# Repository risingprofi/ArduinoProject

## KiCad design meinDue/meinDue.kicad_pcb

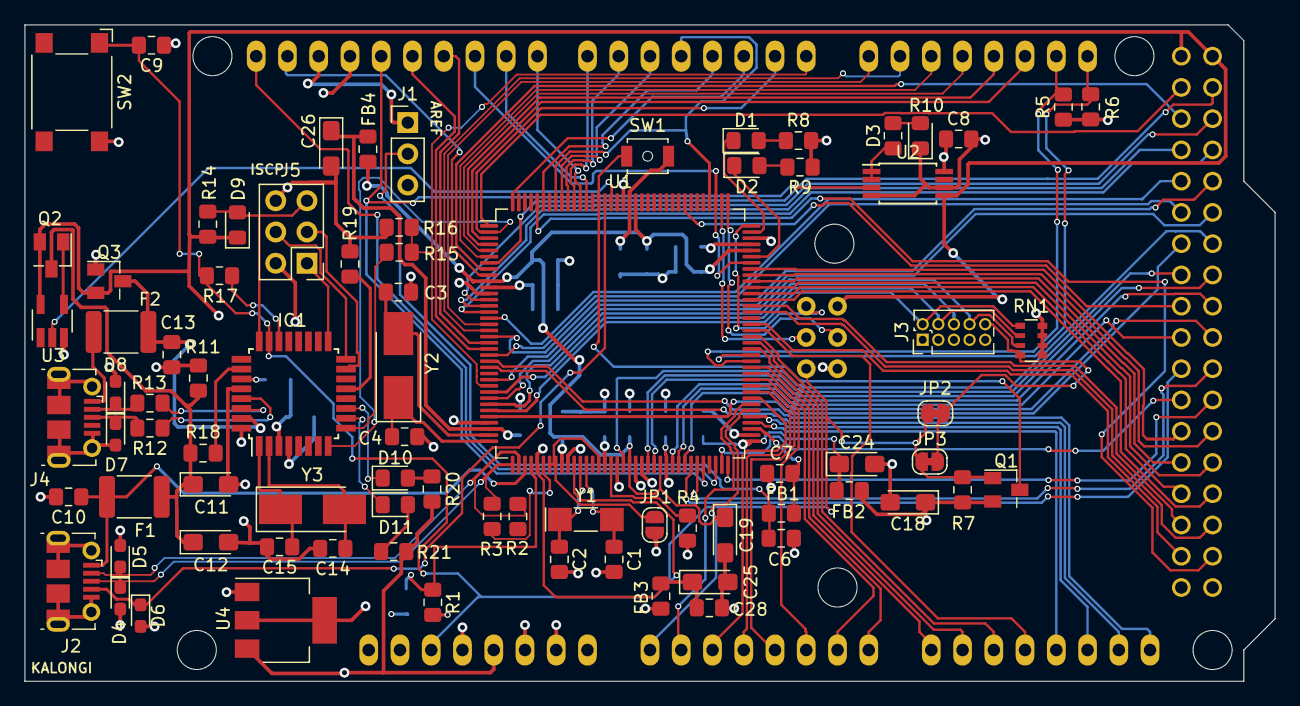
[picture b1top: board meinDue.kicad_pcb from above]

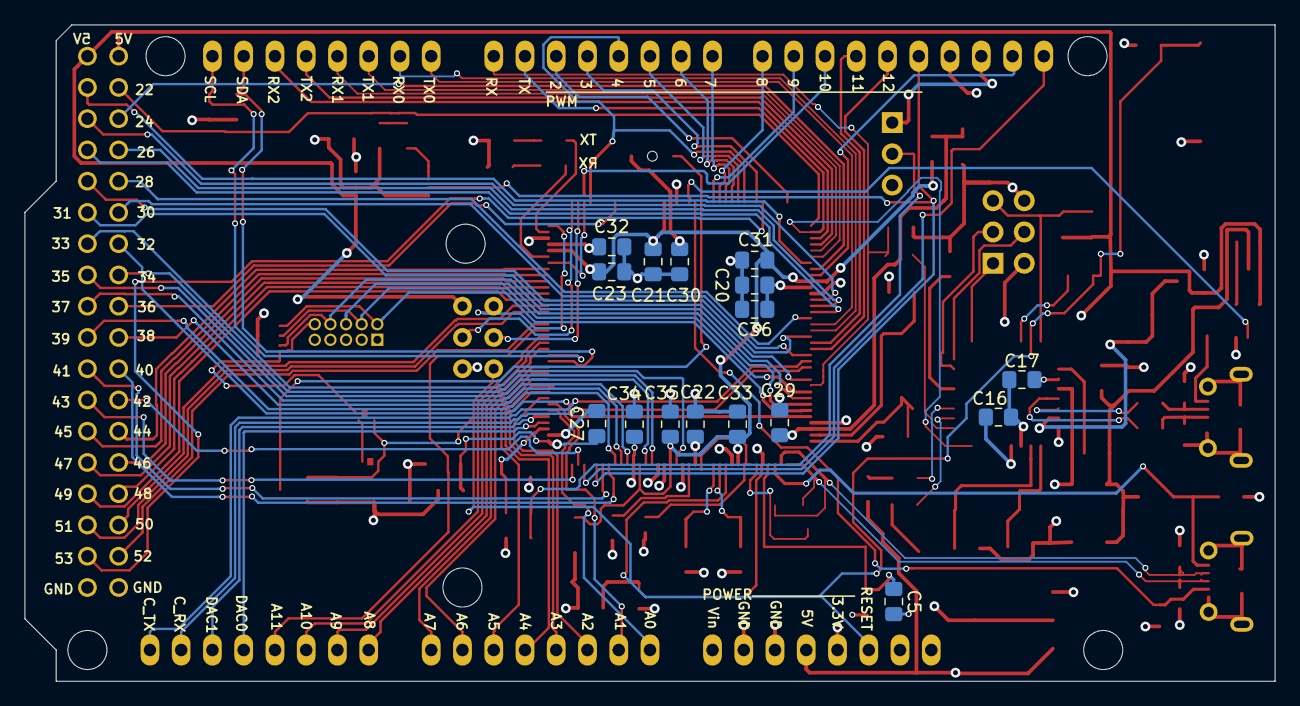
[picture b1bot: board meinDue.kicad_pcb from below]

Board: 4 copper layers, 101.6 x 53.3 mm, 97 parts (16 on the bottom side), 134 nets.

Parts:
C1, C2, C3, C4, C5, C14, C15: 22pF; C_0805_2012Metric_Pad1.15x1.40mm_HandSolder
C6, C7, C8, C9, C13, C16, C20, C21, C22, C23, C27, C28, C29, C30, C31, C32, C33, C34, C35, C36: 100nF; C_0805_2012Metric_Pad1.15x1.40mm_HandSolder
C10: 10nF; C_0805_2012Metric_Pad1.15x1.40mm_HandSolder
C11, C12, C18, C19, C24, C25, C26: 10uF; CP_EIA-3216-18_Kemet-A_Pad1.58x1.35mm_HandSolder
C17: 1uF; C_0805_2012Metric_Pad1.15x1.40mm_HandSolder
D1, D2, D3, D10, D11: YELLOW; LED_0805_2012Metric_Pad1.15x1.40mm_HandSolder
D4, D5, D6, D7, D8: D_TVS; D_0603_1608Metric_Pad1.05x0.95mm_HandSolder
D9: D; D_0805_2012Metric_Pad1.15x1.40mm_HandSolder
F1, F2: Polyfuse; Fuse_1812_4532Metric_Pad1.30x3.40mm_HandSolder
FB1, FB2, FB3, FB4: Ferrite_Bead; L_0805_2012Metric_Pad1.15x1.40mm_HandSolder
IC1: ATMEGA16U2; TQFP-32_7x7mm_P0.8mm
J1: Conn_01x03; PinHeader_1x03_P2.54mm_Vertical
J2, J4: USB_B_Micro; USB_Micro-B_Molex-105017-0001
J3: Conn_02x05_Odd_Even; PinHeader_2x05_P1.27mm_Vertical
J5: ICSP; PinHeader_2x03_P2.54mm_Vertical
JP1: SolderJumper_2_Open; SolderJumper-2_P1.3mm_Open_RoundedPad1.0x1.5mm
JP2, JP3: SolderJumper_2_Bridged; SolderJumper-2_P1.3mm_Bridged_RoundedPad1.0x1.5mm
Q1, Q2, Q3: Q_PMOS_GSD; SuperSOT-3
R1: 6k8 1%; R_0805_2012Metric_Pad1.15x1.40mm_HandSolder
R2, R3: 39R 1%; R_0805_2012Metric_Pad1.15x1.40mm_HandSolder
R4: 100K; R_0805_2012Metric_Pad1.15x1.40mm_HandSolder
R5, R6, R15: 1K5; R_0805_2012Metric_Pad1.15x1.40mm_HandSolder
R7, R11, R14, R19: 10K; R_0805_2012Metric_Pad1.15x1.40mm_HandSolder
R8, R9, R10, R17, R18, R20, R21: 1K; R_0805_2012Metric_Pad1.15x1.40mm_HandSolder
R12, R13: 22R; R_0805_2012Metric_Pad1.15x1.40mm_HandSolder
R16: 2K7; R_0805_2012Metric_Pad1.15x1.40mm_HandSolder
RN1: 100K; R_Array_Convex_4x0603
SHIELD1: ARDUINO_DUE_SHIELD - SPI; ARDUINO_DUE_SHIELD
SW1: SW_SPST; SW_SPST_B3U-1000P-B
SW2: SW_SPST; SW_SPST_Omron_B3FS-100xP
U1: ATSAM3X8E; LQFP-144_20x20mm_P0.5mm
U2: LM358; TSSOP-8_4.4x3mm_P0.65mm
U3: 74LVC1G04; SOT-23-5_HandSoldering
U4: NCP1117ST33T3G; SOT-223-3_TabPin2
Y1: ABS07L 32.768kHz; Crystal_SMD_MicroCrystal_CC5V-T1A-2Pin_4.1x1.5mm_HandSolder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
Y2, Y3: TXC 7A 12MHz 18pf; Crystal_SMD_5032-2Pin_5.0x3.2mm_HandSoldering

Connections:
+3V3: C8.1, C9.1, C18.1, C20.1, C22.1, C30.1, C32.1, C34.1, C36.1, FB2.2, FB3.2, J1.3, J3.1, Q1.2, R4.1, R5.1, R6.1, R7.1, R8.1, R9.1, RN1.5, RN1.6, RN1.7, RN1.8, SHIELD1.3V3, SHIELD1.IO_R, SW1.2, U1.11, U1.52, U1.57, U1.62, U1.105, U1.125, U2.8, U4.2
+5V: C16.1, D9.1, IC1.4, IC1.32, J5.2, Q2.2, Q3.2, R14.1, R20.1, R21.1, SHIELD1.5V, SHIELD1.5V_4, SHIELD1.5V_5, SHIELD1.SP2, U2.5, U3.5, U4.3
/Connectors/D+: D4.1, J2.3, R3.2, U1.37
/Connectors/D-: D5.1, J2.2, R2.2, U1.38
/Connectors/RX: R15.1, R16.1, SHIELD1.0, U1.27
/Connectors/TX: IC1.8, SHIELD1.1, U1.2
/Connectors/UOTGID: D6.1, J2.4, U1.129
/Connectors/USBVCC: C11.1, C12.1, F1.1, Q2.3, R11.1, R18.2
/Connectors/XUSB: C10.1, F1.2, J2.1, U1.39
/MCU/RXL: D2.1, U1.103
/MCU/TXL: D1.1, U1.107
/MCU/UOTGVBOF: U1.128, U3.2
/MCU/VDDANA: C24.1, C27.1, FB2.1, U1.73
/MCU/VDDOUT: C19.1, C21.1, C23.1, C31.1, C33.1, C35.1, FB4.2, U1.10, U1.45, U1.56, U1.61, U1.104, U1.124
/MCU/VDDOUTMI: C25.1, C28.1, FB3.1, U1.41
/MCU/VDDPLL: C26.1, C29.1, FB4.1, U1.34
/MCU/\ERASE_CMD: C9.2, IC1.23, JP2.2, JP3.2, Q1.1, R7.2, R17.1, SHIELD1.RST, SHIELD1.SP5, SW2.1, U1.47
/Mega16U2/16U2_TX: IC1.9, R15.2
/Mega16U2/MISO: IC1.17, J5.1
/Mega16U2/MOSI: IC1.16, J5.4
/Mega16U2/RD+: IC1.29, R12.1
/Mega16U2/RD+_CONN: D8.1, J4.2, R13.2
/Mega16U2/RD-: IC1.30, R13.1
/Mega16U2/RD-_CONN: D7.1, J4.3, R12.2
/Mega16U2/RESET_CMD: IC1.22, R17.2
/Mega16U2/RXL: D11.1, IC1.10
/Mega16U2/SCK: IC1.15, J5.3
/Mega16U2/TXL: D10.1, IC1.11
/Mega16U2/USBVCCU2: C13.1, F2.1, IC1.31, Q3.3
/Mega16U2/USBVCCU2_CONN: F2.2, J4.1
/Mega16U2/USB_BOOT_UNABLE: IC1.13, R19.2
/Mega16U2/XTAL1: C15.1, IC1.1, Y3.1
/Mega16U2/XTAL2: C14.1, IC1.2, Y3.2
AD0: SHIELD1.AD0, U1.78
AD1: SHIELD1.AD1, U1.79
AD2: SHIELD1.AD2, U1.80
AD3: SHIELD1.AD3, U1.81
AD4: SHIELD1.AD4, U1.82
AD5: SHIELD1.AD5, U1.83
AD6: SHIELD1.AD6, U1.84
AD7: SHIELD1.AD7, U1.85
AD8: SHIELD1.AD8, U1.88
AD9: SHIELD1.AD9, U1.89
AD10: SHIELD1.AD10, U1.90
AD11_TXD3: SHIELD1.AD11, U1.91
AD14_RXD3: SHIELD1.52, U1.92
AREF: J1.1, SHIELD1.AREF
CANRX0: SHIELD1.C_RX, U1.24
CANTX0: SHIELD1.C_TX, U1.23
CANTX1_I0: SHIELD1.53, U1.140
DAC0_CANRX1: SHIELD1.DAC0, U1.76
DAC1: SHIELD1.DAC1, U1.77
GND: C1.2, C2.2, C3.2, C4.2, C5.2, C6.2, C7.2, C8.2, C10.2, C11.2, C12.2, C13.2, C14.2, C15.2, C16.2, C17.2, C18.2, C19.2, C20.2, C21.2, C22.2, C23.2, C24.2, C25.2, C26.2, C27.2, C28.2, C29.2, C30.2, C31.2, C32.2, C33.2, C34.2, C35.2, C36.2, D3.1, D4.2, D5.2, D6.2, D7.2, D8.2, IC1.3, IC1.28, J2.5, J2.6, J3.3, J3.5, J3.9, J4.5, J4.6, J5.6, JP1.1, Q3.1, R1.2, R11.2, R16.2, R19.1, SHIELD1.GND1, SHIELD1.GND2, SHIELD1.GND3, SHIELD1.GND4, SHIELD1.GND5, SHIELD1.SP6, SW2.2, U1.12, U1.33, U1.46, U1.54, U1.58, U1.74, U1.106, U1.126, U2.4, U2.6, U3.3, U4.1
JTAG_RESET: J3.10, JP2.1, JP3.1, RN1.4
JTAG_TCK: J3.4, RN1.2, U1.28
JTAG_TD0: J3.6, U1.30
JTAG_TDI: J3.8, RN1.3, U1.29
JTAG_TMS: J3.2, RN1.1, U1.31
MISO: SHIELD1.SP1, U1.108
MOSI: SHIELD1.SP4, U1.109
unnamed: C1.1, U1.49, Y1.2
unnamed: C2.1, U1.48, Y1.1
unnamed: C3.1, U1.35, Y2.2
unnamed: C4.1, U1.36, Y2.1
unnamed: C5.1, R1.1, U1.40
unnamed: C6.1, FB1.2, J1.2
unnamed: C7.1, FB1.1, U1.75
unnamed: C17.1, IC1.27
unnamed: D1.2, R8.2
unnamed: D2.2, R9.2
unnamed: D3.2, R10.1
unnamed: D9.2, IC1.24, J5.5, R14.2
unnamed: D10.2, R20.2
unnamed: D11.2, R21.2
unnamed: IC1.26, R18.1
unnamed: JP1.2, U1.43, U1.44, U1.51
unnamed: Q1.3, SW1.1, U1.130
unnamed: Q2.1, U3.4
unnamed: R3.1, U1.42
unnamed: R4.2, U1.53
unnamed: R10.2, U2.1, U2.2
PIN22: SHIELD1.22, U1.1
PIN23: SHIELD1.23, U1.7
PIN24: SHIELD1.24, U1.8
PIN25: SHIELD1.25, U1.13
PIN26: SHIELD1.26, U1.14
PIN27: SHIELD1.27, U1.15
PIN28: SHIELD1.28, U1.16
PIN29: SHIELD1.29, U1.19
PIN30: SHIELD1.30, U1.22
PIN31: SHIELD1.31, U1.26
PIN32: SHIELD1.32, U1.32
PIN33: SHIELD1.33, U1.55
PIN34: SHIELD1.34, U1.59
PIN35: SHIELD1.35, U1.60
PIN36: SHIELD1.36, U1.116
PIN37: SHIELD1.37, U1.63
PIN38: SHIELD1.38, U1.64
PIN39: SHIELD1.39, U1.65
PIN40: SHIELD1.40, U1.66
PIN41: SHIELD1.41, U1.67
PIN42: SHIELD1.42, U1.71
PIN43: SHIELD1.43, U1.72
PIN44: SHIELD1.44, U1.101
PIN45: SHIELD1.45, U1.100
PIN46: SHIELD1.46, U1.99
PIN47: SHIELD1.47, U1.98
PIN48: SHIELD1.48, U1.97
PIN49: SHIELD1.49, U1.96
PIN50: SHIELD1.50, U1.95
PIN51: SHIELD1.51, U1.94
PWM2: SHIELD1.2, U1.144
PWM3: SHIELD1.3, U1.139
PWM5: SHIELD1.5, U1.136
PWM6: SHIELD1.6, U1.135
PWM7: SHIELD1.7, U1.134
PWM8: SHIELD1.8, U1.133
PWM9: SHIELD1.9, U1.132
PWM11: SHIELD1.11, U1.20
PWM12: SHIELD1.12, U1.21
PWM13: SHIELD1.13, U1.68, U2.3
RXD0: SHIELD1.15, U1.18
RXD1: SHIELD1.17, U1.5
RXD2: SHIELD1.19, U1.3
SCK: SHIELD1.SP3, U1.110
SCL0-3: R6.2, SHIELD1.21, U1.87
SCL1: SHIELD1.SCL1, U1.70
SDA0-3: R5.2, SHIELD1.20, U1.86
SDA1: SHIELD1.SDA1, U1.9
SS0_PWM10: SHIELD1.10, U1.102, U1.111
SS1_PWM4: SHIELD1.4, U1.112, U1.137
TXD0: SHIELD1.14, U1.17
TXD1: SHIELD1.16, U1.6
TXD2: SHIELD1.18, U1.4

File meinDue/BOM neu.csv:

ID;Bezeichner;Gehäuse;Stückzahl;Bezeichnung;Anbieter und Referenz
1;J3;PinHeader_2x05_P1.27mm_Vertical;1;Conn_02x05_Odd_Even;
2;SHIELD1;ARDUINO_DUE_SHIELD;1;ARDUINO_DUE_SHIELD - SPI;
3;D9;D_0805_2012Metric_Pad1.15x1.40mm_HandSolder;1;D;
4;Y3,Y2;Crystal_SMD_5032-2Pin_5.0x3.2mm_HandSoldering;2;TXC 7A 12MHz 18pf;
5;Y1;Crystal_SMD_MicroCrystal_CC5V-T1A-2Pin_4.1x1.5mm_HandSoldering;1;ABS07L 32.768kHz;
6;U4;SOT-223-3_TabPin2;1;NCP1117ST33T3G;
7;U3;SOT-23-5_HandSoldering;1;74LVC1G04;
8;U2;TSSOP-8_4.4x3mm_P0.65mm;1;LM358;
9;U1;LQFP-144_20x20mm_P0.5mm;1;ATSAM3X8E;
10;SW2;SW_SPST_Omron_B3FS-100xP;1;SW_SPST;
11;SW1;SW_SPST_B3U-1000P-B;1;SW_SPST;
12;RN1;R_Array_Convex_4x0603;1;100K;
13;R21,R20,R18,R17,R10,R9,R8;R_0805_2012Metric_Pad1.15x1.40mm_HandSolder;7;1K;
14;R19,R14,R11,R7;R_0805_2012Metric_Pad1.15x1.40mm_HandSolder;4;10K;
15;R16;R_0805_2012Metric_Pad1.15x1.40mm_HandSolder;1;2K7;
16;R15,R6,R5;R_0805_2012Metric_Pad1.15x1.40mm_HandSolder;3;1K5;
17;R13,R12;R_0805_2012Metric_Pad1.15x1.40mm_HandSolder;2;22R;
18;R4;R_0805_2012Metric_Pad1.15x1.40mm_HandSolder;1;100K;
19;R3,R2;R_0805_2012Metric_Pad1.15x1.40mm_HandSolder;2;39R 1%;
20;R1;R_0805_2012Metric_Pad1.15x1.40mm_HandSolder;1;6k8 1%;
21;Q3,Q2,Q1;SuperSOT-3;3;Q_PMOS_GSD;
22;JP3,JP2;SolderJumper-2_P1.3mm_Bridged_RoundedPad1.0x1.5mm;2;SolderJumper_2_Bridged;
23;JP1;SolderJumper-2_P1.3mm_Open_RoundedPad1.0x1.5mm;1;SolderJumper_2_Open;
24;J5;PinHeader_2x03_P2.54mm_Vertical;1;ICSP;
25;J4,J2;USB_Micro-B_Molex-105017-0001;2;USB_B_Micro;
26;J1;PinHeader_1x03_P2.54mm_Vertical;1;Conn_01x03;
27;IC1;TQFP-32_7x7mm_P0.8mm;1;ATMEGA16U2;
28;FB4,FB3,FB2,FB1;L_0805_2012Metric_Pad1.15x1.40mm_HandSolder;4;Ferrite_Bead;
29;F2,F1;Fuse_1812_4532Metric_Pad1.30x3.40mm_HandSolder;2;Polyfuse;
30;D11,D10,D3,D2,D1;LED_0805_2012Metric_Pad1.15x1.40mm_HandSolder;5;YELLOW;
31;D8,D7,D6,D5,D4;D_0603_1608Metric_Pad1.05x0.95mm_HandSolder;5;D_TVS;
32;C36,C35,C34,C33,C32,C31,C30,C29,C28,C27,C23,C22,C21,C20,C16,C13,C9,C8,C7,C6;C_0805_2012Metric_Pad1.15x1.40mm_HandSolder;20;100nF;
33;C26,C25,C24,C19,C18,C12,C11;CP_EIA-3216-18_Kemet-A_Pad1.58x1.35mm_HandSolder;7;10uF;
34;C17;C_0805_2012Metric_Pad1.15x1.40mm_HandSolder;1;1uF;
35;C15,C14,C5,C4,C3,C2,C1;C_0805_2012Metric_Pad1.15x1.40mm_HandSolder;7;22pF;
36;C10;C_0805_2012Metric_Pad1.15x1.40mm_HandSolder;1;10nF;

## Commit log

2020-06-23 Add files via Upload
    Wahlpflichtfach Menküc
